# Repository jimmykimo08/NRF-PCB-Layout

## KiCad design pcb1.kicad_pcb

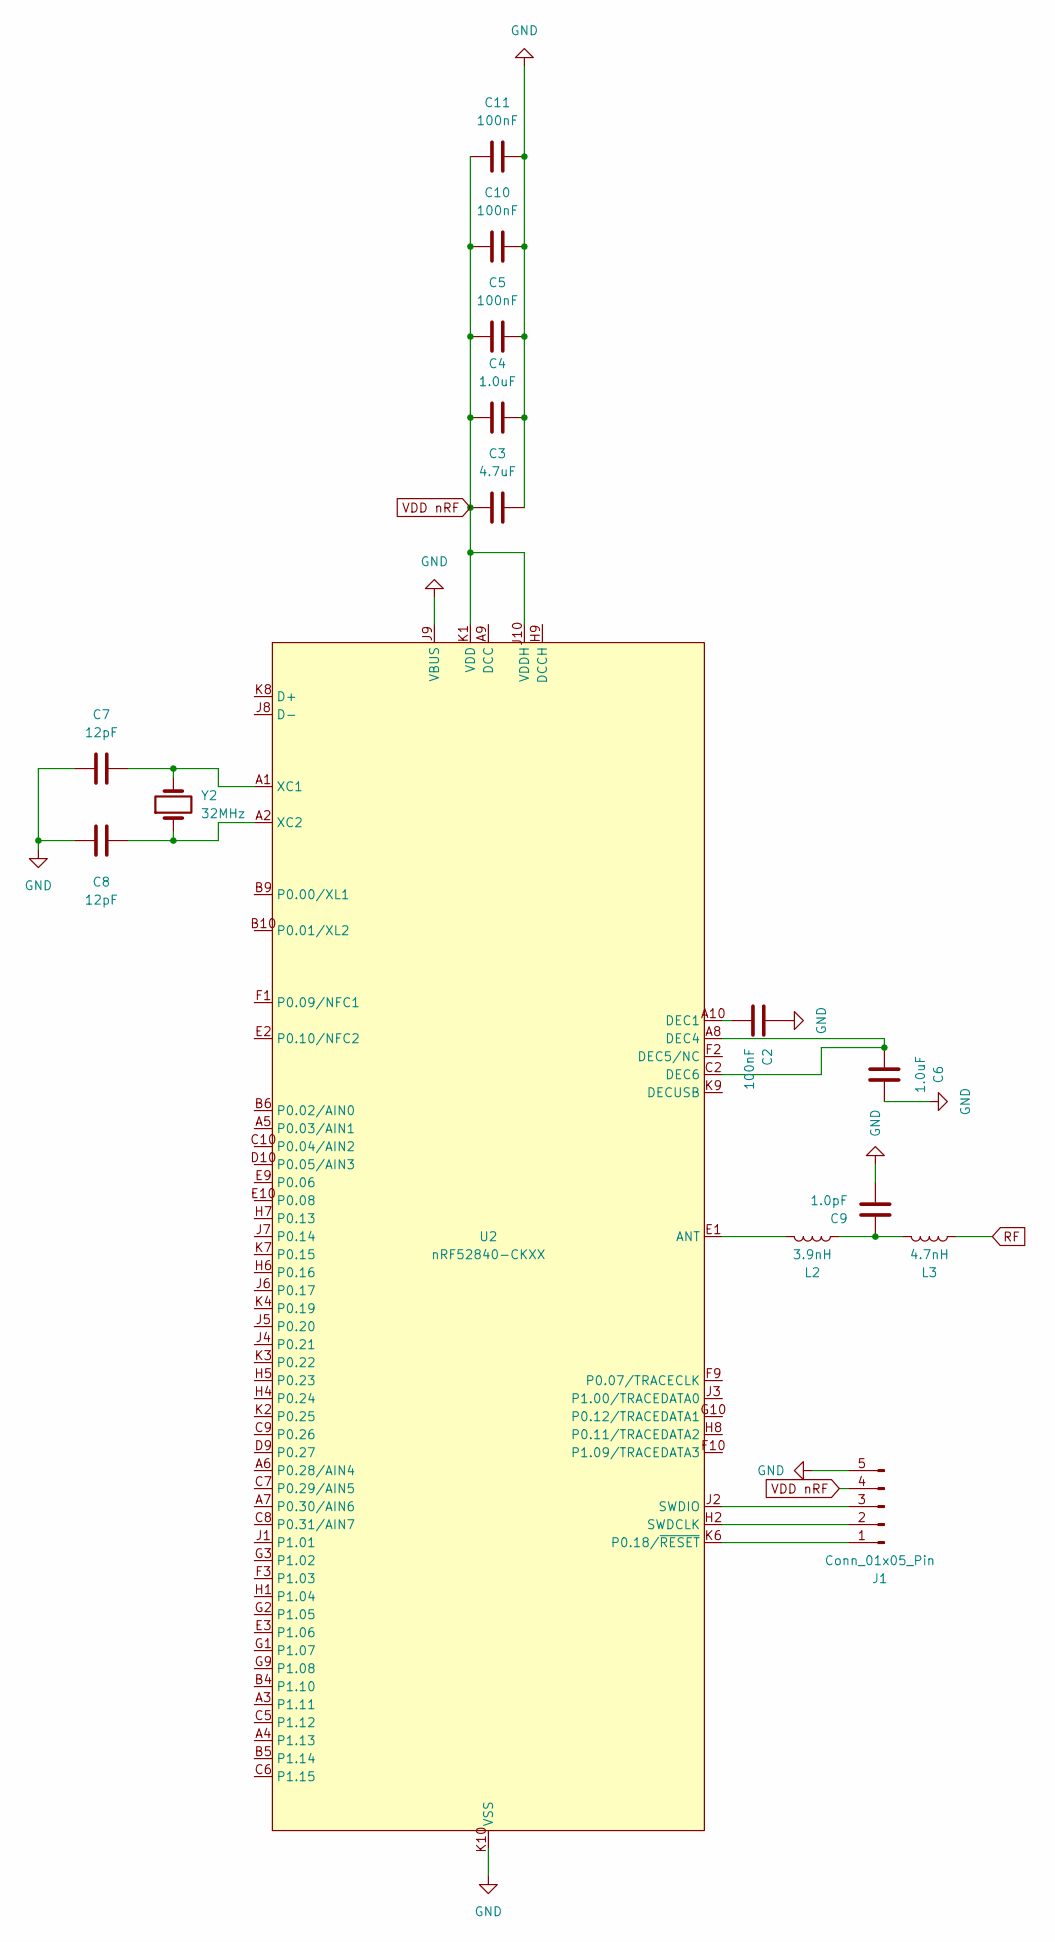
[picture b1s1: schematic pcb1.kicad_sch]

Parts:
C2, C5, C10, C11: 100nF; C_0201_0603Metric
C3: 4.7uF; C_0603_1608Metric
C4, C6: 1.0uF; C_0603_1608Metric
C7, C8: 12pF; C_0201_0603Metric
C9: 1.0pF; C_0201_0603Metric
J1: Conn_01x05_Pin; PinHeader_1x05_P2.54mm_Vertical
L2: 3.9nH; L_0201_0603Metric
L3: 4.7nH; L_0201_0603Metric
U2: nRF52840-CKXX; BGA-94_10x10_3.544x3.607mm
Y2: 32MHz; Crystal_SMD_2016-4Pin_2.0x1.6mm

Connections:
GND: C2.1, C3.2, C4.2, C5.2, C6.2, C7.1, C8.2, C9.2, C10.2, C11.2, J1.5, U2.B7 (VSS), U2.C1 (VSS_PA), U2.C4 (VSS), U2.D3 (VSS), U2.D4 (VSS), U2.D5 (VSS), U2.D6 (VSS), U2.D7 (VSS), U2.D8 (VSS), U2.E4 (VSS), U2.E5 (VSS), U2.E6 (VSS), U2.E7 (VSS), U2.E8 (VSS), U2.F4 (VSS), U2.F5 (VSS), U2.F6 (VSS), U2.F7 (VSS), U2.F8 (VSS), U2.G4 (VSS), U2.G5 (VSS), U2.G6 (VSS), U2.G7 (VSS), U2.G8 (VSS), U2.J9 (VBUS), U2.K10 (VSS); also elsewhere on the board
unnamed: C9.1, L2.1, L3.2
unnamed 2: J1.1, U2.K6 (P0.18/~RESET); also elsewhere on the board
unnamed 3: J1.2, U2.H2 (SWDCLK); also elsewhere on the board
unnamed 4: J1.3, U2.J2 (SWDIO); also elsewhere on the board
unnamed 5: L2.2, U2.E1 (ANT); also elsewhere on the board
unnamed 6: C2.2, U2.A10 (DEC1); also elsewhere on the board
unnamed 7: C6.1, U2.A8 (DEC4), U2.C2 (DEC6); also elsewhere on the board
unnamed 8: C7.2, U2.A1 (XC1), Y2.2; also elsewhere on the board
unnamed 9: C8.1, U2.A2 (XC2), Y2.1; also elsewhere on the board
RF: L3.1
VDD nRF: C3.1, C4.1, C5.1, C10.1, C11.1, J1.4, U2.B3 (VDD), U2.B8 (VDD), U2.H10 (VDD), U2.J10 (VDDH), U2.K1 (VDD), U2.K5 (VDD); also elsewhere on the board

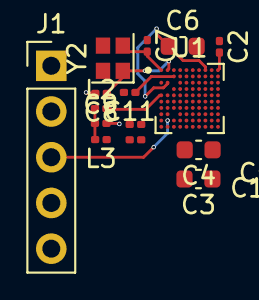
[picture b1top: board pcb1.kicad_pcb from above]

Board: 2 copper layers, 15 parts (0 on the bottom side), 11 nets.

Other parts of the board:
U1: nRF52840-CKXX; BGA-94_10x10_3.544x3.607mm

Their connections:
GND: U1.B7 (VSS), U1.C1 (VSS_PA), U1.C4 (VSS), U1.D3 (VSS), U1.D4 (VSS), U1.D5 (VSS), U1.D6 (VSS), U1.D7 (VSS), U1.D8 (VSS), U1.E4 (VSS), U1.E5 (VSS), U1.E6 (VSS), U1.E7 (VSS), U1.E8 (VSS), U1.F4 (VSS), U1.F5 (VSS), U1.F6 (VSS), U1.F7 (VSS), U1.F8 (VSS), U1.G4 (VSS), U1.G5 (VSS), U1.G6 (VSS), U1.G7 (VSS), U1.G8 (VSS), U1.J9 (VBUS), U1.K10 (VSS); also elsewhere on the board
unnamed 2: U1.K6 (P0.18/~RESET); also elsewhere on the board
unnamed 3: U1.H2 (SWDCLK); also elsewhere on the board
unnamed 4: U1.J2 (SWDIO); also elsewhere on the board
unnamed 5: U1.E1 (ANT); also elsewhere on the board
unnamed 6: U1.A10 (DEC1); also elsewhere on the board
unnamed 7: U1.A8 (DEC4), U1.C2 (DEC6); also elsewhere on the board
unnamed 8: U1.A1 (XC1); also elsewhere on the board
unnamed 9: U1.A2 (XC2); also elsewhere on the board
VDD nRF: U1.B3 (VDD), U1.B8 (VDD), U1.H10 (VDD), U1.J10 (VDDH), U1.K1 (VDD), U1.K5 (VDD); also elsewhere on the board
